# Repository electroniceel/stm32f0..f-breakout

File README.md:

STM32F0..F (TSSOP20) Breakout Module
====================================

A breakout module for STM32F0 microcontrollers in TSSOP20 footprint.

Basic Features
--------------

* Focus on small footprint and direct access to all pins.
* Provides a 8 pin Micro-MaTch header for easy access to SWD and UART.
* Pushbutton for Reset (press <1 second) and starting the bootloader (press >3 seconds).
* Onboard LDO regulator (standard SOT-23-5) can be used for VDD and VDDA, just VDD or disabled completely.
* Use of a crystal (SMT 3.2x2.5mm) is optional.
* Options can be configured using solder bridges.
* Power LED and User LED (on PA0, PF1 or disconnected).
* Size: 20x32mm or 10x8 pins in the standard 2.54mm raster

Currently supported microcontrollers
------------------------------------

* STM32F030F4
* STM32F031F4
* STM32F031F6
* STM32F038F6
* STM32F042F4 (USB header must be connected externally)
* STM32F042F6 (USB header must be connected externally)
* STM32F070F6 (USB header must be connected externally)

Schematics & Layout
-------------------

Schematics & Layout were done in KiCAD.

[Schematics as PDF](https://github.com/electroniceel/stm32f0..f-breakout/raw/master/schematics.pdf)

Picture
-------

License
-------

This work is licensed under a [Creative Commons Attribution 4.0 International License](https://creativecommons.org/licenses/by/4.0/).

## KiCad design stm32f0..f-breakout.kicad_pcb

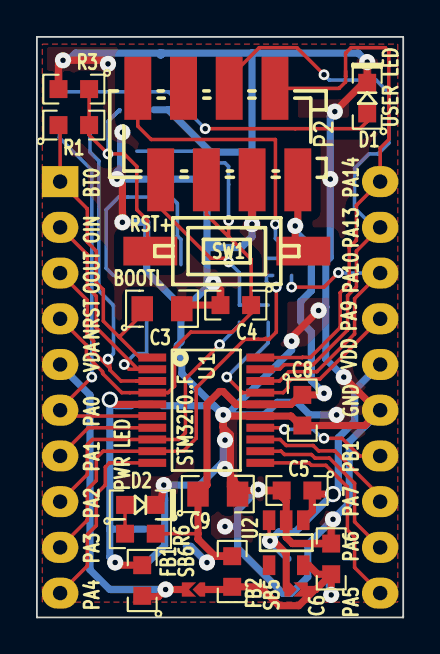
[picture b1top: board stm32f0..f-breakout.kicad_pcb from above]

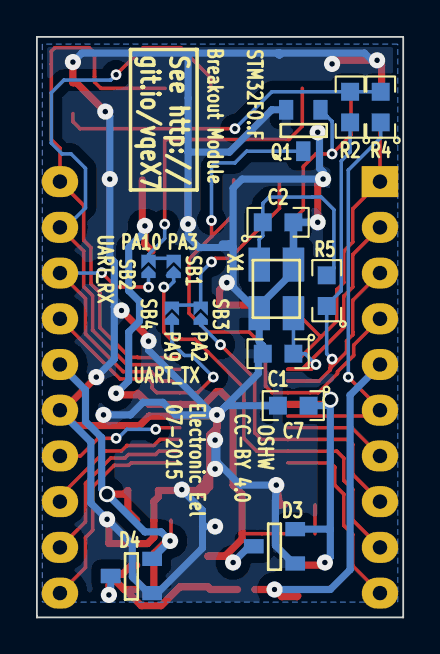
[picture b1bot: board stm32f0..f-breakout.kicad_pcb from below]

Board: 2 copper layers, 20.4 x 32.2 mm, 35 parts (16 on the bottom side), 29 nets.

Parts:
C1, C2: 20pF; SMD0603-wide-C
C3, C9: 4.7µF; SMD0805-wide-C
C4, C8: 100nF; SMD0603-wide-C
C5, C6, C7: 1µF; SMD0603-wide-C
D1: LED; SMD0603-wide-diode
D2: LED green; SMD0603-wide-diode
D3, D4: BAT54S; SOT-23
FB1, FB2: MMZ1608B601C; SMD0603-wide
P1, P3: CONN_01X10; Pin_Header_Straight_1x10
P2: MicroMatch_8pin; Conn-Micromatch-SMD-8
Q1: BSS138; SOT-23
R1: 820K; SMD0603-wide-R
R2, R4: 330R; SMD0603-wide-R
R3: 10K; SMD0603-wide-R
R5: 0R; SMD0603-wide-R
R6: 1K; SMD0603-wide-R
SB1, SB2, SB3, SB4, SB5, SB6: Solderbridge
SW1: SW_PUSH-SPST-NO; Push-Button-SMD-6.0x3.5mm
U1: STM32F030F4; TSSOP-20_4.4x6.5mm_Pitch0.65mm
U2: XC6204B332MR; SOT-23-5
X1: 12MHz; smd-xtal-3225

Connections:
+3.3VADC: C7.1, D3.2, FB1.2, U1.5
+3V3: C8.1, C9.1, D3.3, FB2.2, P2.1, R6.1, SW1.1, U1.16
/BOOT0: C3.1, P1.1, R1.1, U1.1
/NRST: C4.1, P1.4, P2.5, Q1.3, U1.4
/OSC_IN: C1.1, P1.2, U1.2, X1.1
/OSC_OUT: P1.3, R2.1, R5.1, U1.3
/PA0: P1.6, R4.1, U1.6
/PA2: P1.8, SB3.1, U1.8
/PA3: P1.9, SB1.1, U1.9
/PA9: P3.7, SB4.1, U1.17
/PA10: P3.8, SB2.1, U1.18
/SWCLK: P2.2, P3.10, U1.20
/SWDIO: P2.4, P3.9, U1.19
/SWITCHED: Q1.1, R1.2, R3.1, SW1.2
/UART_RX: P2.8, SB1.2, SB2.2
/UART_TX: P2.7, SB3.2, SB4.2
/USER_LED: D1.1, R2.2, R4.2
/VDDA_IN: FB1.1, P1.5, SB6.2
/VDD_IN: C5.1, D4.2, P3.6, SB5.1, U2.1, U2.3
/VREG_OUT: C6.1, D4.3, FB2.1, SB5.2, SB6.1, U2.5
GND: C1.2, C2.2, C3.2, C4.2, C5.2, C6.2, C7.2, C8.2, C9.2, D1.2, D2.2, D3.1, D4.1, P2.3, P3.5, Q1.2, R3.2, U1.15, U2.2, X1.3
unnamed: C2.1, R5.2, X1.2
unnamed: D2.1, R6.2
unnamed: P1.7, U1.7
unnamed: P1.10, U1.10
unnamed: P3.1, U1.11
unnamed: P3.2, U1.12
unnamed: P3.3, U1.13
unnamed: P3.4, U1.14

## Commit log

2015-07-02 fix markdown syntax
2018-01-04 move to more permissive CC-BY license
2018-01-04 add actual kicad design files
2018-01-04 add pictures and schematics.pdf
2018-01-04 link picture and pdf in readme
2018-01-05 improve readme

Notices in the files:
stm32f0..f-breakout.kicad_pcb:
CC-BY 4.0
